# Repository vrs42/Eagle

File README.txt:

==============================================

  E A G L E - L A Y O U T - S O F T W A R E
       Information about Version 4.11

==============================================

Updating from older versions
----------------------------

IMPORTANT: If you are updating from an older version of EAGLE, please make sure
*********  you read the file doc/UPDATE.txt entirely before
           working with this new version!

Tutorial
--------

The EAGLE tutorial in PDF format can be found in the \english\tutorial
subdirectory on the EAGLE CD-ROM.
If you have downloaded EAGLE from CadSoft's homepage you may also want
to download the tutorial file.

Running the CAM Processor in batch mode
---------------------------------------

Since Windows programs give up their connection to the console they
have been started from, you can use the file 'eaglecon.exe' (located
in the 'demo' subdirectory on the CD-ROM) if you want to run the
CAM Processor from a batch file. This version of EAGLE is exactly
the same as the 'eagle.exe', except that it doesn't disconnect from
the console. Type 'eaglecon -?' for a list of CAM Processor options.

Uninstalling the Program
------------------------

In case you want to uninstall EAGLE you can click on the
"unInstallShield" icon, which has been created during installation.
This will remove all EAGLE files and registry entries, except for
files that have been created *after* the installation, like e.g.
project, schematic or board files. In that case the uninstall program
issues a message telling you that it could not remove all files.
Remove the remaining files manually from your EAGLE program directory
(default: C:\Program files\EAGLE).

Files with names like "DeIsL1.isu" in the EAGLE program directory are
necessary for the uninstallation process and should not be deleted.

Displaying and printing texts
-----------------------------

Some Windows graphics and printer drivers appear to be unable to display
texts the way EAGLE needs them to be (any size and mixed colors). If this
is the case on your system, you should either install a newer graphics
and/or printer driver, or set "Options/User interface/Always vector font"
in the EAGLE Control Panel to 'on'. With this option EAGLE always uses its
builtin vector font, which is guaranteed to work.

Printing with the PRINT Command
-------------------------------

When printing to b/w printers (like e.g. laser printers) objects may
not be visible very good. The reason for this is that the Windows
printer driver attempts to draw colors as shades of gray, which can
lead to very light shades of gray. In such cases you should use the
option "Black" to produce a pure b/w print.

Multi-Monitor Operation
-----------------------

Currently EAGLE works on multi-monitor systems only if all monitors form one
large desktop.

Mouse wheel
-----------

When a board/schematic pair is loaded and one of the windows is minimized, it
can happen that the mouse wheel won't work to zoom in and out of an editor
window. In such a case you can just click anywhere on the desktop and back on
the EAGLE editor window to activate mouse wheel support.

Octagon apertures in Gerber RS-274X format
------------------------------------------

The various Gerber viewers on the market have different ideas about how to
display octagon apertures in RS-274X format. There all all kinds of
interpretations of the diameter and rotation.
When generating octagon apertures in RS-274X format, EAGLE assumes that the
viewer will interpret the diameter as the distance between two opposite
corners, and that it has to be rotated by 22.5 degrees to achieve the proper
alignment. In case your specific viewer interprets these data differently
you can adjust this to your viewer's special needs in the file 'eagle.def'.

IMPORTANT: Before sending data in RS-274X format to your board house you should
make sure you ask them how *their* software will interpret octagon data.

                           ===================
=========================== SALES INFORMATION =================================
                           ===================

EAGLE is a program of:   CadSoft Computer, Inc.
                         801 S. Federal Hwy., Suite 201
                         Delray Beach, FL 33483-5185
                         Phone:  (561) 274-8355
                         Fax:    (561) 274-8218
                         E-Mail: info@cadsoftusa.com
                         Web:    http://www.cadsoftusa.com

EAGLE is available for Linux and Windows platforms.

===============================================================================
"Linux" is a registered trademark of Linus Torvalds.
"Windows" is a registered trademark of Microsoft Corporation.
===============================================================================

Copyright (c) 2003 CadSoft Computer, Inc. - All rights reserved

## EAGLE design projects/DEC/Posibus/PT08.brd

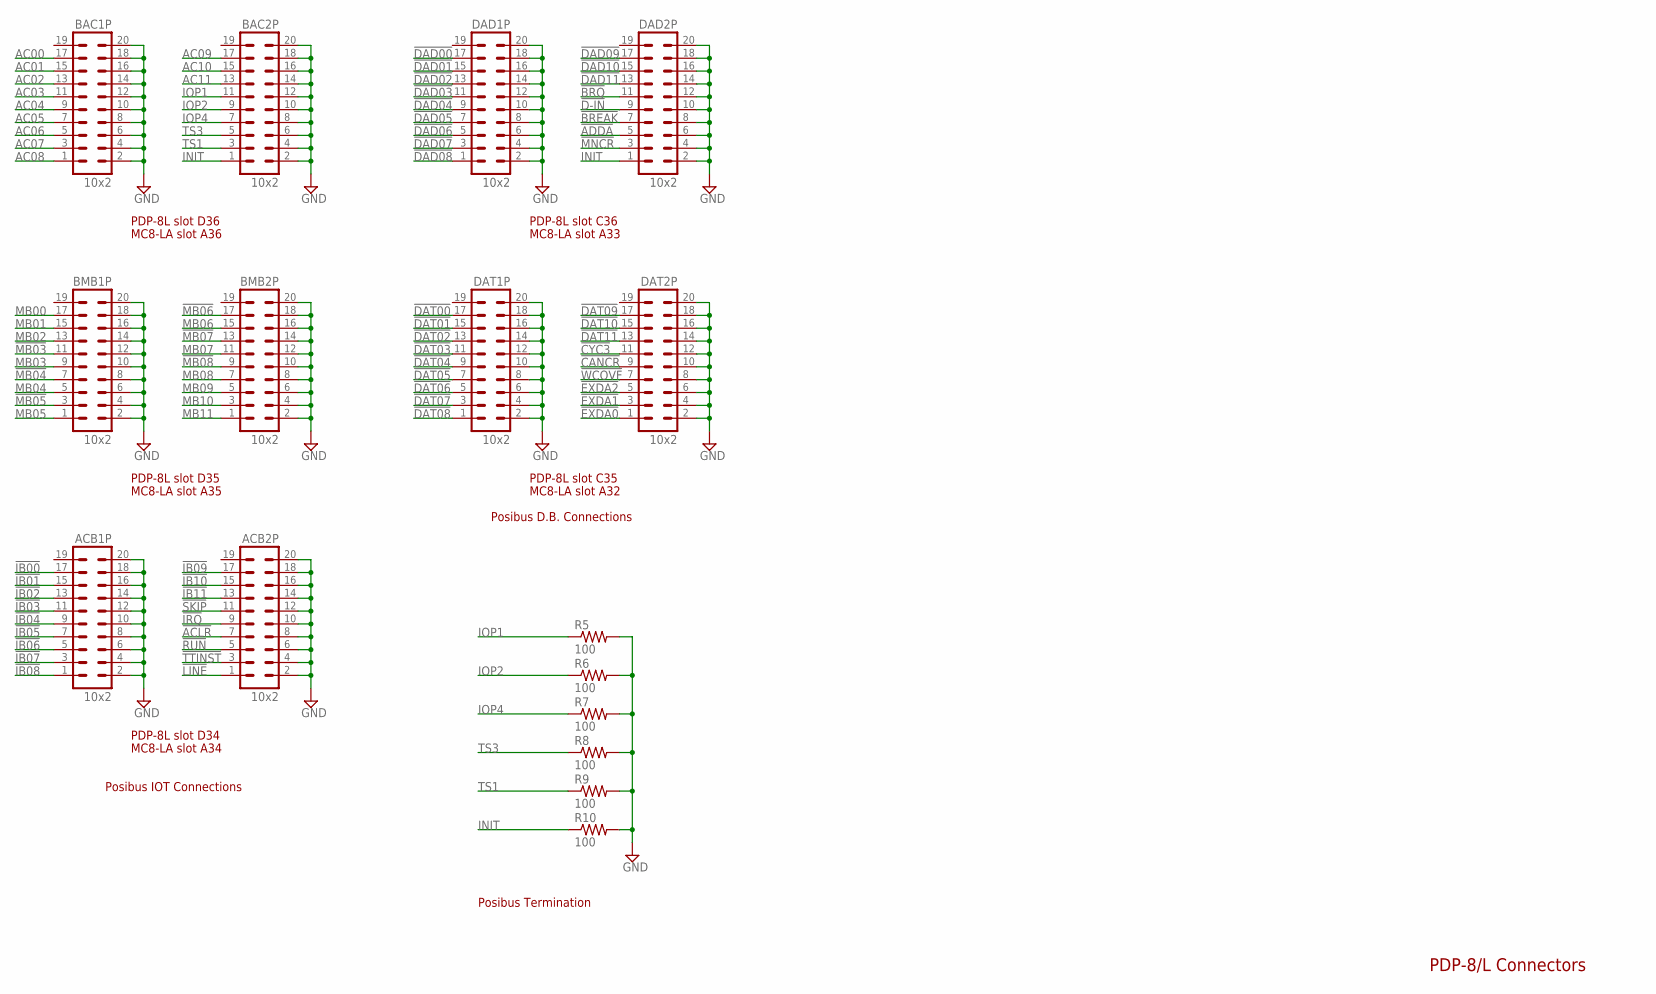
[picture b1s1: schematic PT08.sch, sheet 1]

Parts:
ACB1P, ACB2P: 10x2; MA10-2
BAC1P, BAC2P: 10x2; MA10-2
BMB1P, BMB2P: 10x2; MA10-2
DAD1P, DAD2P: 10x2; MA10-2
DAT1P, DAT2P: 10x2; MA10-2
R5, R6, R7, R8, R9, R10: 100; R1206

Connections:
!ACLR: ACB2P.7; also elsewhere on the board
!ADDA: DAD2P.5
!BREAK: DAD2P.7
!BRQ: DAD2P.11
!CANCR: DAT2P.9
!CYC3: DAT2P.11
!D-IN: DAD2P.9
!DAD00: DAD1P.17
!DAD01: DAD1P.15
!DAD02: DAD1P.13
!DAD03: DAD1P.11
!DAD04: DAD1P.9
!DAD05: DAD1P.7
!DAD06: DAD1P.5
!DAD07: DAD1P.3
!DAD08: DAD1P.1
!DAD09: DAD2P.17
!DAD10: DAD2P.15
!DAD11: DAD2P.13
!DAT00: DAT1P.17
!DAT01: DAT1P.15
!DAT02: DAT1P.13
!DAT03: DAT1P.11
!DAT04: DAT1P.9
!DAT05: DAT1P.7
!DAT06: DAT1P.5
!DAT07: DAT1P.3
!DAT08: DAT1P.1
!DAT09: DAT2P.17
!DAT10: DAT2P.15
!DAT11: DAT2P.13
!EXDA0: DAT2P.1
!EXDA1: DAT2P.3
!EXDA2: DAT2P.5
!IB00: ACB1P.17; also elsewhere on the board
!IB01: ACB1P.15; also elsewhere on the board
!IB02: ACB1P.13; also elsewhere on the board
!IB03: ACB1P.11; also elsewhere on the board
!IB04: ACB1P.9; also elsewhere on the board
!IB05: ACB1P.7; also elsewhere on the board
!IB06: ACB1P.5; also elsewhere on the board
!IB07: ACB1P.3; also elsewhere on the board
!IB08: ACB1P.1; also elsewhere on the board
!IB09: ACB2P.17; also elsewhere on the board
!IB10: ACB2P.15; also elsewhere on the board
!IB11: ACB2P.13; also elsewhere on the board
!IRQ: ACB2P.9; also elsewhere on the board
!LINE: ACB2P.1; also elsewhere on the board
!MB03: BMB1P.11
!MB04: BMB1P.7
!MB05: BMB1P.3
!MB06: BMB2P.17
!MB07: BMB2P.13
!MB08: BMB2P.9
!MNCR: DAD2P.3
!RUN: ACB2P.5; also elsewhere on the board
!SKIP: ACB2P.11; also elsewhere on the board
!TTINST: ACB2P.3; also elsewhere on the board
!WCOVF: DAT2P.7
AC00: BAC1P.17; also elsewhere on the board
AC01: BAC1P.15; also elsewhere on the board
AC02: BAC1P.13; also elsewhere on the board
AC03: BAC1P.11; also elsewhere on the board
AC04: BAC1P.9; also elsewhere on the board
AC05: BAC1P.7; also elsewhere on the board
AC06: BAC1P.5; also elsewhere on the board
AC07: BAC1P.3; also elsewhere on the board
AC08: BAC1P.1; also elsewhere on the board
AC09: BAC2P.17; also elsewhere on the board
AC10: BAC2P.15; also elsewhere on the board
AC11: BAC2P.13; also elsewhere on the board
GND: ACB1P.2, ACB1P.4, ACB1P.6, ACB1P.8, ACB1P.10, ACB1P.12, ACB1P.14, ACB1P.16, ACB1P.18, ACB1P.20, ACB2P.2, ACB2P.4, ACB2P.6, ACB2P.8, ACB2P.10, ACB2P.12, ACB2P.14, ACB2P.16, ACB2P.18, ACB2P.20, BAC1P.2, BAC1P.4, BAC1P.6, BAC1P.8, BAC1P.10, BAC1P.12, BAC1P.14, BAC1P.16, BAC1P.18, BAC1P.20, BAC2P.2, BAC2P.4, BAC2P.6, BAC2P.8, BAC2P.10, BAC2P.12, BAC2P.14, BAC2P.16, BAC2P.18, BAC2P.20, BMB1P.2, BMB1P.4, BMB1P.6, BMB1P.8, BMB1P.10, BMB1P.12, BMB1P.14, BMB1P.16, BMB1P.18, BMB1P.20, BMB2P.2, BMB2P.4, BMB2P.6, BMB2P.8, BMB2P.10, BMB2P.12, BMB2P.14, BMB2P.16, BMB2P.18, BMB2P.20, DAD1P.2, DAD1P.4, DAD1P.6, DAD1P.8, DAD1P.10, DAD1P.12, DAD1P.14, DAD1P.16, DAD1P.18, DAD1P.20, DAD2P.2, DAD2P.4, DAD2P.6, DAD2P.8, DAD2P.10, DAD2P.12, DAD2P.14, DAD2P.16, DAD2P.18, DAD2P.20, DAT1P.2, DAT1P.4, DAT1P.6, DAT1P.8, DAT1P.10, DAT1P.12, DAT1P.14, DAT1P.16, DAT1P.18, DAT1P.20, DAT2P.2, DAT2P.4, DAT2P.6, DAT2P.8, DAT2P.10, DAT2P.12, DAT2P.14, DAT2P.16, DAT2P.18, DAT2P.20, R5.2, R6.2, R7.2, R8.2, R9.2, R10.2; also elsewhere on the board
INIT: BAC2P.1, DAD2P.1, R10.1; also elsewhere on the board
IOP1: BAC2P.11, R5.1; also elsewhere on the board
IOP2: BAC2P.9, R6.1; also elsewhere on the board
IOP4: BAC2P.7, R7.1; also elsewhere on the board
MB00: BMB1P.17; also elsewhere on the board
MB01: BMB1P.15; also elsewhere on the board
MB02: BMB1P.13; also elsewhere on the board
MB03: BMB1P.9; also elsewhere on the board
MB04: BMB1P.5; also elsewhere on the board
MB05: BMB1P.1; also elsewhere on the board
MB06: BMB2P.15; also elsewhere on the board
MB07: BMB2P.11; also elsewhere on the board
MB08: BMB2P.7; also elsewhere on the board
MB09: BMB2P.5; also elsewhere on the board
MB10: BMB2P.3; also elsewhere on the board
MB11: BMB2P.1; also elsewhere on the board
TS1: BAC2P.3, R9.1; also elsewhere on the board
TS3: BAC2P.5, R8.1; also elsewhere on the board

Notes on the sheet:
Posibus IOT Connections
Posibus D.B. Connections
PDP-8/L Connectors
PDP-8L slot D35
MC8-LA slot A35
PDP-8L slot D36
MC8-LA slot A36
PDP-8L slot D34
MC8-LA slot A34
PDP-8L slot C36
MC8-LA slot A33
PDP-8L slot C35
MC8-LA slot A32
Posibus Termination

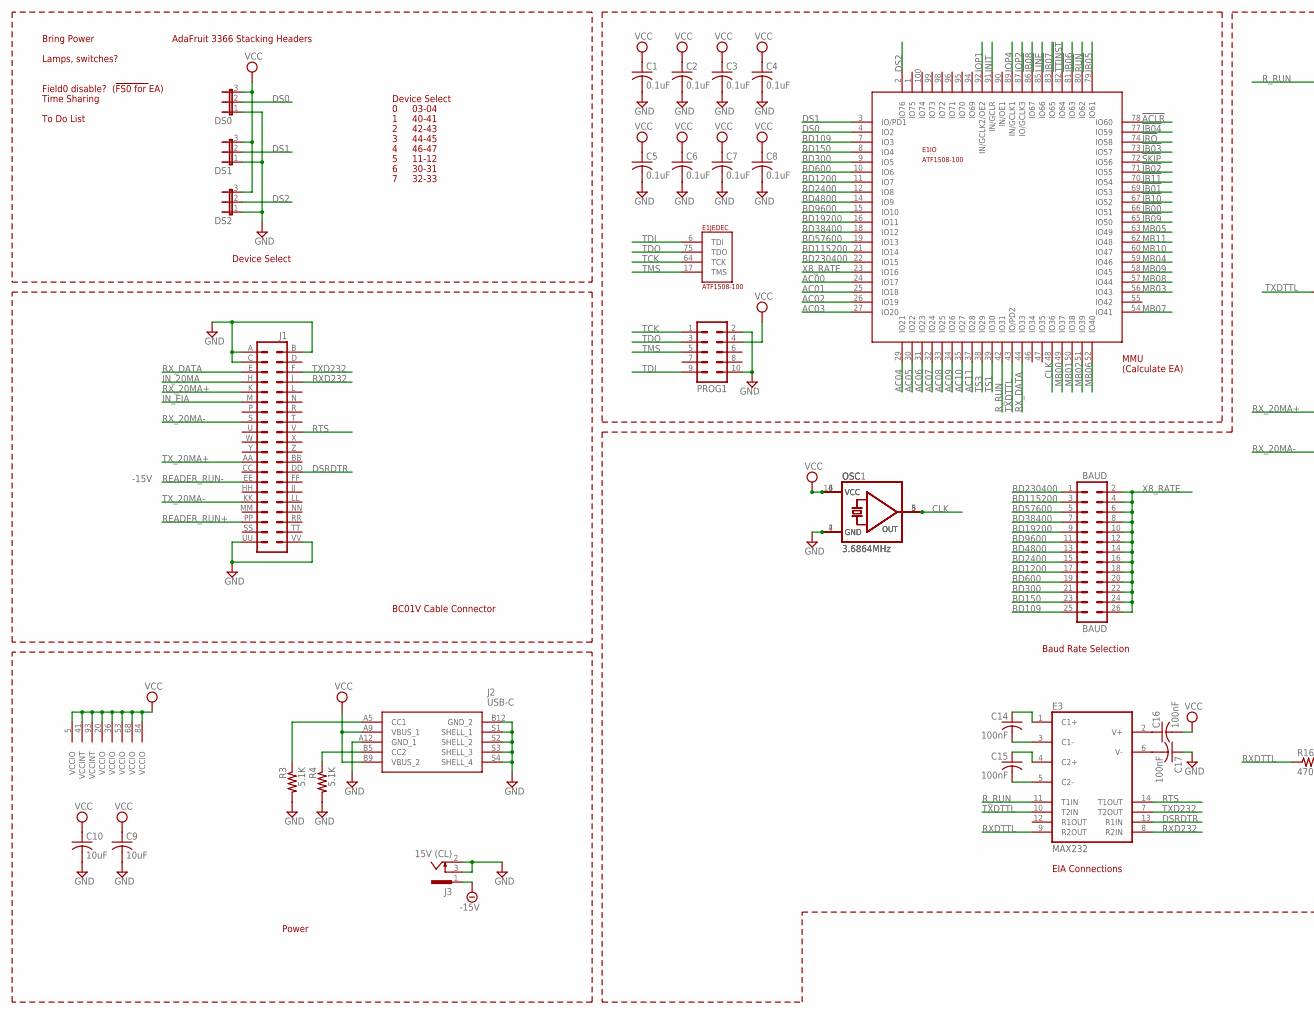
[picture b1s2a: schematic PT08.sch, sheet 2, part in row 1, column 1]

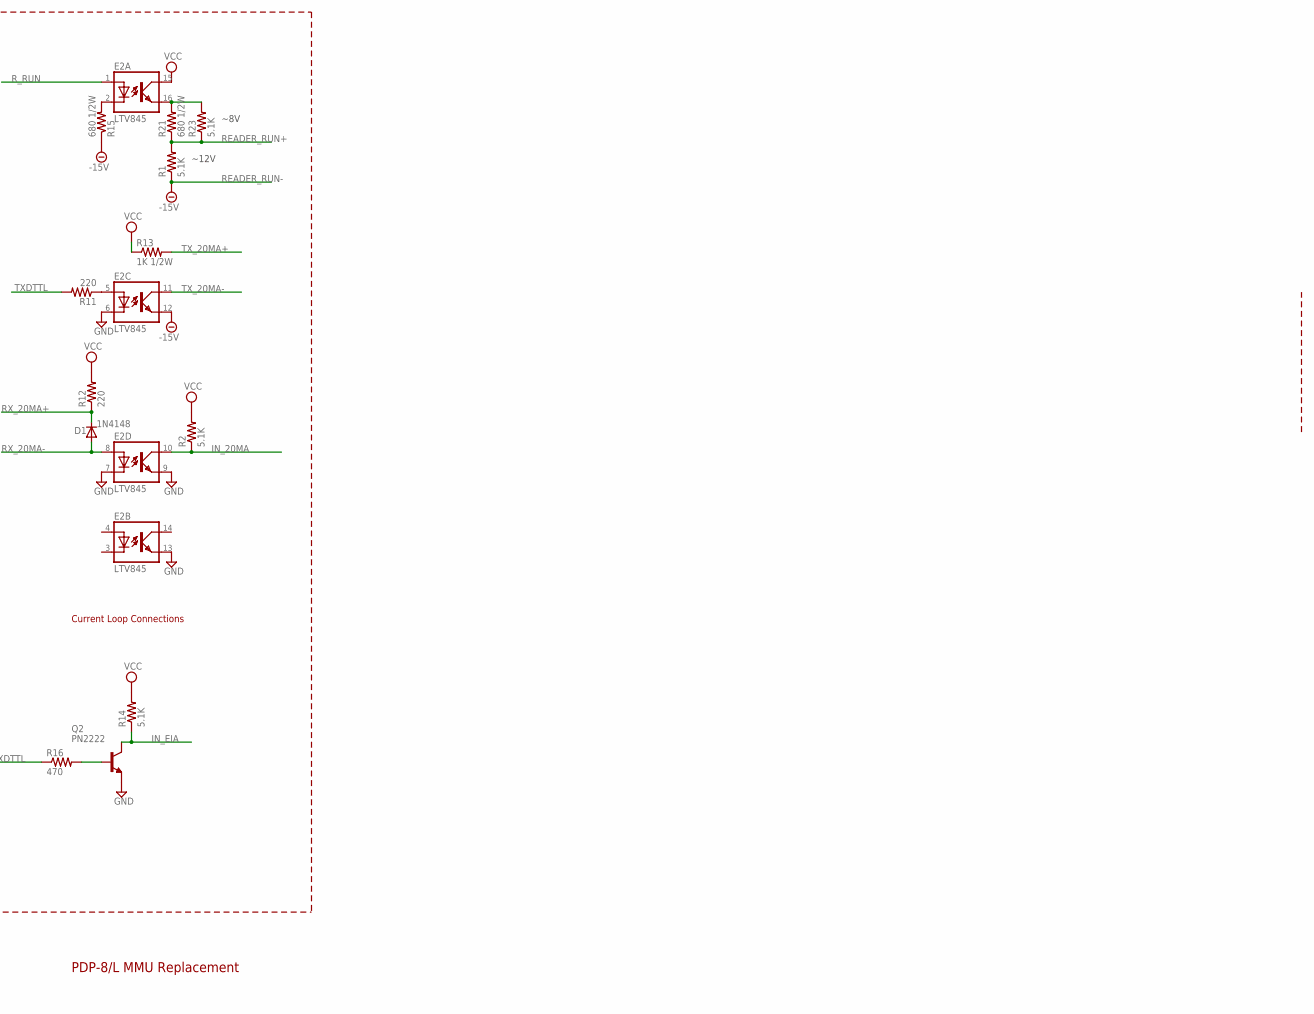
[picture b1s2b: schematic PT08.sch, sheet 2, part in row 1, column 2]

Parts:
BAUD: BAUD; MA13-2
C1, C2, C3, C4, C5, C6, C7, C8: 0.1uF; C0805
C9, C10: 10uF; C0805
C14, C15, C16, C17: 100nF; C0805
D1: 1N4148; SOD323-W
DS0, DS1, DS2: JP2
E1: ATF1508-100; PQFP-100
E2: LTV845; DIL16
E3: MAX232; DIL16
J1: DEC40PINH
J2: USB-C; USB497000A
J3: 15V (CL); SCD-014-A
OSC: 3.6864MHz; DIL08S
OSC1: 3.6864MHz; DIL14S
PROG1: ML10
Q2: PN2222; SOT23-EBC
R1, R2, R3, R4, R14, R23: 5.1K; R0805
R11, R12: 220; R0805
R13: 1K 1/2W; 0207/10
R15, R21: 680 1/2W; 0207/10
R16: 470; R0805

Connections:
!ACLR: E1.78 (IO60); also elsewhere on the board
!IB00: E1.66 (IO51); also elsewhere on the board
!IB01: E1.69 (IO53); also elsewhere on the board
!IB02: E1.71 (IO55); also elsewhere on the board
!IB03: E1.73 (IO57); also elsewhere on the board
!IB04: E1.77 (IO59); also elsewhere on the board
!IB05: E1.79 (IO61); also elsewhere on the board
!IB06: E1.81 (IO63); also elsewhere on the board
!IB07: E1.83 (IO65); also elsewhere on the board
!IB08: E1.86 (IO67); also elsewhere on the board
!IB09: E1.65 (IO50); also elsewhere on the board
!IB10: E1.67 (IO52); also elsewhere on the board
!IB11: E1.70 (IO54); also elsewhere on the board
!IRQ: E1.74 (IO58); also elsewhere on the board
!LINE: E1.85 (IO66); also elsewhere on the board
!RUN: E1.80 (IO62); also elsewhere on the board
!SKIP: E1.72 (IO56); also elsewhere on the board
!TTINST: E1.82 (IO64); also elsewhere on the board
-15V: E2.12 (EMIT), J1.EE (27), J3.1, R1.1, R15.1
AC00: E1.24 (IO17); also elsewhere on the board
AC01: E1.25 (IO18); also elsewhere on the board
AC02: E1.26 (IO19); also elsewhere on the board
AC03: E1.27 (IO20); also elsewhere on the board
AC04: E1.29 (IO21); also elsewhere on the board
AC05: E1.30 (IO22); also elsewhere on the board
AC06: E1.31 (IO23); also elsewhere on the board
AC07: E1.32 (IO24); also elsewhere on the board
AC08: E1.33 (IO25); also elsewhere on the board
AC09: E1.34 (IO26); also elsewhere on the board
AC10: E1.35 (IO27); also elsewhere on the board
AC11: E1.37 (IO28); also elsewhere on the board
BD109: BAUD.25, E1.7 (IO3)
BD150: BAUD.23, E1.8 (IO4)
BD300: BAUD.21, E1.9 (IO5)
BD600: BAUD.19, E1.10 (IO6)
BD1200: BAUD.17, E1.11 (IO7)
BD2400: BAUD.15, E1.12 (IO8)
BD4800: BAUD.13, E1.14 (IO9)
BD9600: BAUD.11, E1.15 (IO10)
BD19200: BAUD.9, E1.16 (IO11)
BD38400: BAUD.7, E1.18 (IO12)
BD57600: BAUD.5, E1.19 (IO13)
BD115200: BAUD.3, E1.21 (IO14)
BD230400: BAUD.1, E1.22 (IO15)
CLK: E1.48 (IO36), OSC.5 (OUT), OSC1.8 (OUT)
DS0: DS0.2, E1.4 (IO2)
DS1: DS1.2, E1.3 (IO/PD1)
DS2: DS2.2, E1.2 (IO76)
DSRDTR: E3.13 (R1IN), J1.DD (26)
GND: C1.2, C2.2, C3.2, C4.2, C5.2, C6.2, C7.2, C8.2, C9.2, C10.2, C17.1, DS0.1, DS1.1, DS2.1, E1.13 (GND), E1.28 (GND), E1.40 (GND), E1.45 (GND), E1.61 (GND), E1.76 (GND), E1.88 (GND), E1.97 (GND), E2.6 (C), E2.7 (C), E2.9 (EMIT), E2.13 (EMIT), E3.15 (GND), J1.A (1), J1.B (2), J1.C (3), J1.UU (39), J1.VV (40), J2.A12 (GND_1), J2.B12 (GND_2), J2.S1 (SHELL_1), J2.S2 (SHELL_2), J2.S3 (SHELL_3), J2.S4 (SHELL_4), J3.2, J3.3, OSC.4 (GND), OSC1.7 (GND), PROG1.2, PROG1.10, Q2.E, R3.2, R4.2; also elsewhere on the board
INIT: E1.91 (IN/GCLR); also elsewhere on the board
IN_20MA: E2.10 (COL), J1.H (7), R2.1
IN_EIA: J1.M (11), Q2.C, R14.1
IOP1: E1.92 (IN/GCLK2/OE2); also elsewhere on the board
IOP2: E1.87 (IO/GCLK3); also elsewhere on the board
IOP4: E1.89 (IN/GCLK1); also elsewhere on the board
MB00: E1.49 (IO37); also elsewhere on the board
MB01: E1.50 (IO38); also elsewhere on the board
MB02: E1.51 (IO39); also elsewhere on the board
MB03: E1.56 (IO43); also elsewhere on the board
MB04: E1.59 (IO46); also elsewhere on the board
MB05: E1.63 (IO49); also elsewhere on the board
MB06: E1.52 (IO40); also elsewhere on the board
MB07: E1.54 (IO41); also elsewhere on the board
MB08: E1.57 (IO44); also elsewhere on the board
MB09: E1.58 (IO45); also elsewhere on the board
MB10: E1.60 (IO47); also elsewhere on the board
MB11: E1.62 (IO48); also elsewhere on the board
unnamed: J2.B5 (CC2), R4.1
unnamed: E2.2 (C), R15.2
unnamed: J2.A5 (CC1), R3.1
unnamed: E2.16 (EMIT), R21.2, R23.2
unnamed: Q2.B, R16.2
unnamed: E2.5 (A), R11.1
unnamed: C17.2, E3.6 (V-)
unnamed: C14.1, E3.1 (C1+)
unnamed: C14.2, E3.3 (C1-)
unnamed: C15.2, E3.5 (C2-)
unnamed: C15.1, E3.4 (C2+)
unnamed: C16.1, E3.2 (V+)
READER_RUN+: J1.PP (35), R1.2, R21.1, R23.1
RTS: E3.14 (T1OUT), J1.V (18)
RXD232: E3.8 (R2IN), J1.J (8)
RXDTTL: E3.9 (R2OUT), R16.1
RX_20MA+: D1.C, J1.K (9), R12.1
RX_20MA-: D1.A, E2.8 (A), J1.S (15)
RX_DATA: E1.44 (IO33), J1.E (5)
R_RUN: E1.42 (IO31), E2.1 (A), E3.11 (T1IN)
TCK: E1.64 (TCK), PROG1.1
TDI: E1.6 (TDI), PROG1.9
TDO: E1.75 (TDO), PROG1.3
TMS: E1.17 (TMS), PROG1.5
TS1: E1.39 (IO30); also elsewhere on the board
TS3: E1.38 (IO29); also elsewhere on the board
TXD232: E3.7 (T2OUT), J1.F (6)
TXDTTL: E1.43 (IO/PD2), E3.10 (T2IN), R11.2
TX_20MA+: J1.AA (23), R13.2
TX_20MA-: E2.11 (COL), J1.KK (31)
VCC: C1.1, C2.1, C3.1, C4.1, C5.1, C6.1, C7.1, C8.1, C9.1, C10.1, C16.2, DS0.3, DS1.3, DS2.3, E1.5 (VCCIO), E1.20 (VCCIO), E1.36 (VCCIO), E1.41 (VCCINT), E1.53 (VCCIO), E1.68 (VCCIO), E1.84 (VCCIO), E1.93 (VCCINT), E2.15 (COL), E3.16 (VCC), J2.A9 (VBUS_1), J2.B9 (VBUS_2), OSC.8 (VCC), OSC1.14 (VCC), PROG1.4, R2.2, R12.2, R13.1, R14.2
X8_RATE: BAUD.2, BAUD.4, BAUD.6, BAUD.8, BAUD.10, BAUD.12, BAUD.14, BAUD.16, BAUD.18, BAUD.20, BAUD.22, BAUD.24, BAUD.26, E1.23 (IO16)

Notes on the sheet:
PDP-8/L MMU Replacement
Bring Power
Lamps, switches?
Field0 disable?
Time Sharing
To Do List
(!FS0 for !EA)
AdaFruit 3366 Stacking Headers
MMU
(Calculate EA)
Power
Device Select
EIA Connections
Current Loop Connections
~8V
~12V
READER_RUN-
BC01V Cable Connector
Baud Rate Selection
03-04
40-41
42-43
44-45
46-47
11-12
30-31
32-33

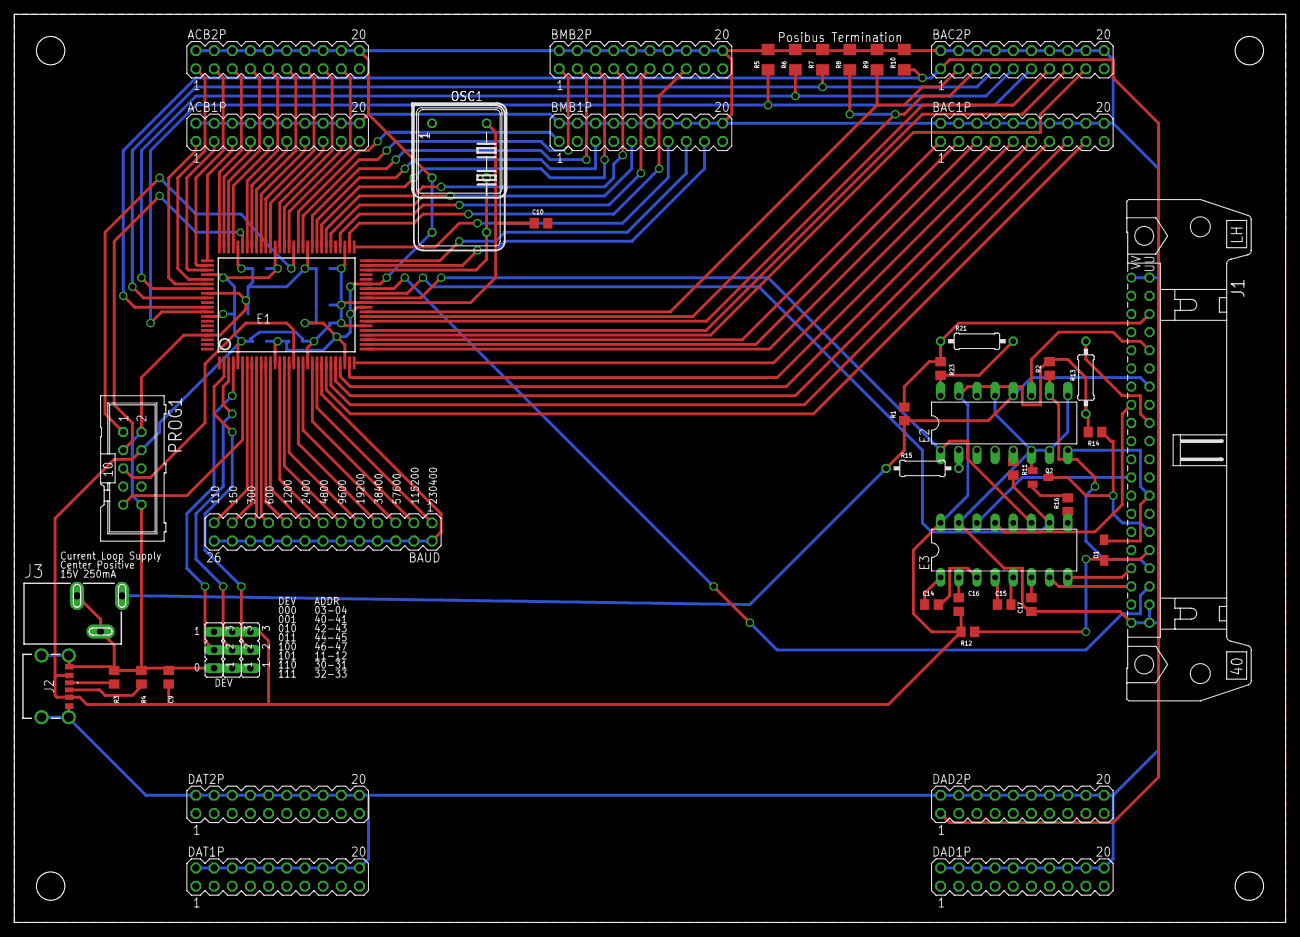
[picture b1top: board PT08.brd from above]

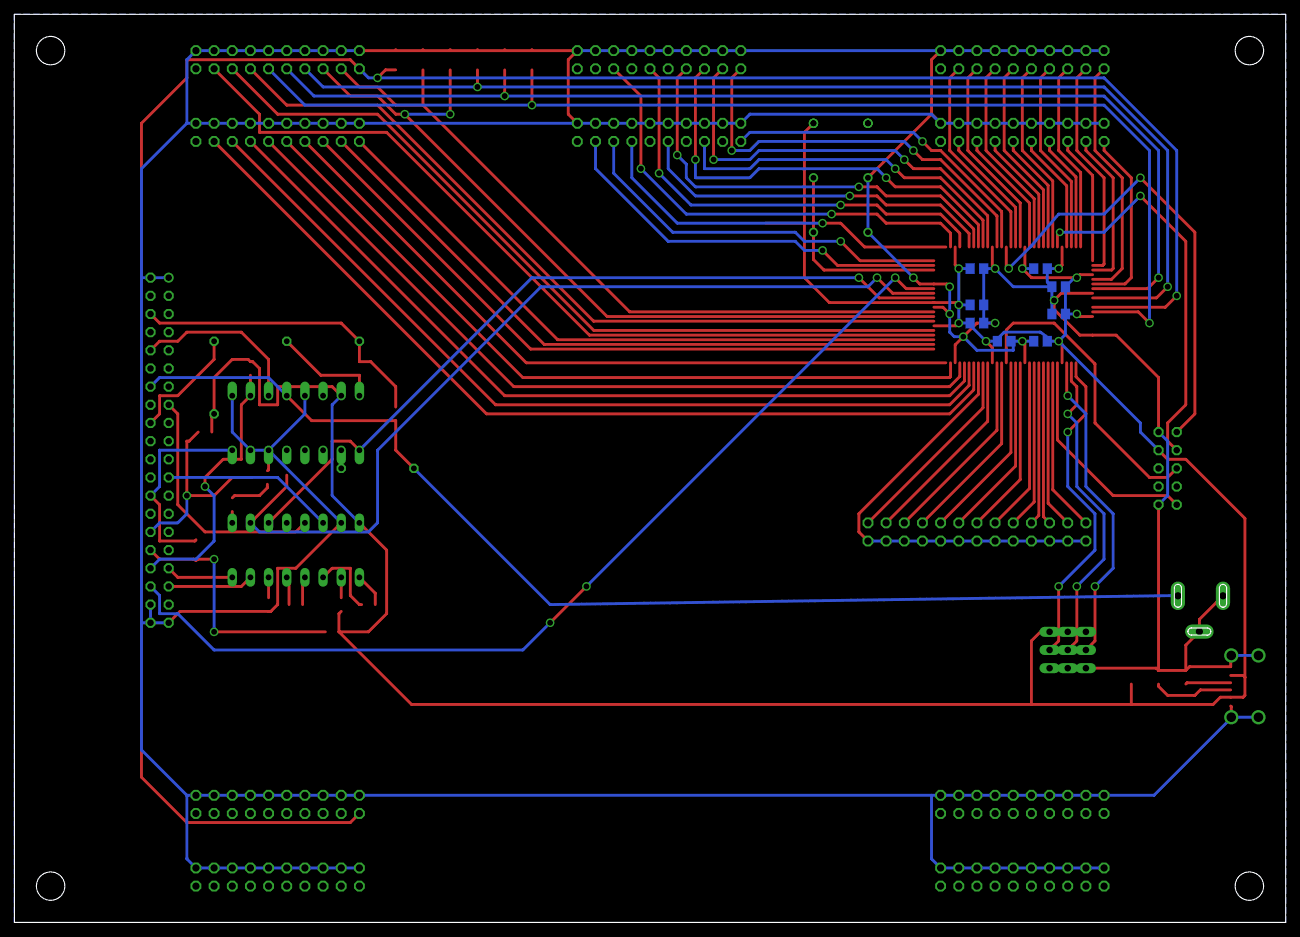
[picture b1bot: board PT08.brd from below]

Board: 2 copper layers, 177.8 x 127.0 mm, 57 parts (8 on the bottom side), 100 nets.

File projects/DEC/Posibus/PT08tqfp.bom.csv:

Comment,Designator,Footprint,PartNo
0.1uF,C5,C0805,C5378
0.1uF,C4,C0805,C5378
0.1uF,C2,C0805,C5378
0.1uF,C6,C0805,C5378
0.1uF,C3,C0805,C5378
ATF1508-100,E1,TQFP-100,C1521282
0.1uF,C1,C0805,C5378
0.1uF,C7,C0805,C5378
0.1uF,C8,C0805,C5378
5.1K,R4,R0805,C27834
5.1K,R3,R0805,C27834
100,R5,R1206,C17901
100,R6,R1206,C17901
100,R7,R1206,C17901
100,R8,R1206,C17901
100,R9,R1206,C17901
100,R10,R1206,C17901
100nF,C14,C0805,C5378
100nF,C15,C0805,C5378
100nF,C16,C0805,C5378
100nF,C17,C0805,C5378
5.1K,R1,R0805,C27834
5.1K,R2,R0805,C27834
220,R11,R0805,C17557
220,R12,R0805,C17557
1N4148,D1,SOD323-W,C2128
5.1K,R23,R0805,C27834
5.1K,R14,R0805,C27834
470,R16,R0805,C17710
PN2222,Q2,SOT23-EBC,C8512
10uF,C9,C0805,C15850
10uF,C10,C0805,C15850

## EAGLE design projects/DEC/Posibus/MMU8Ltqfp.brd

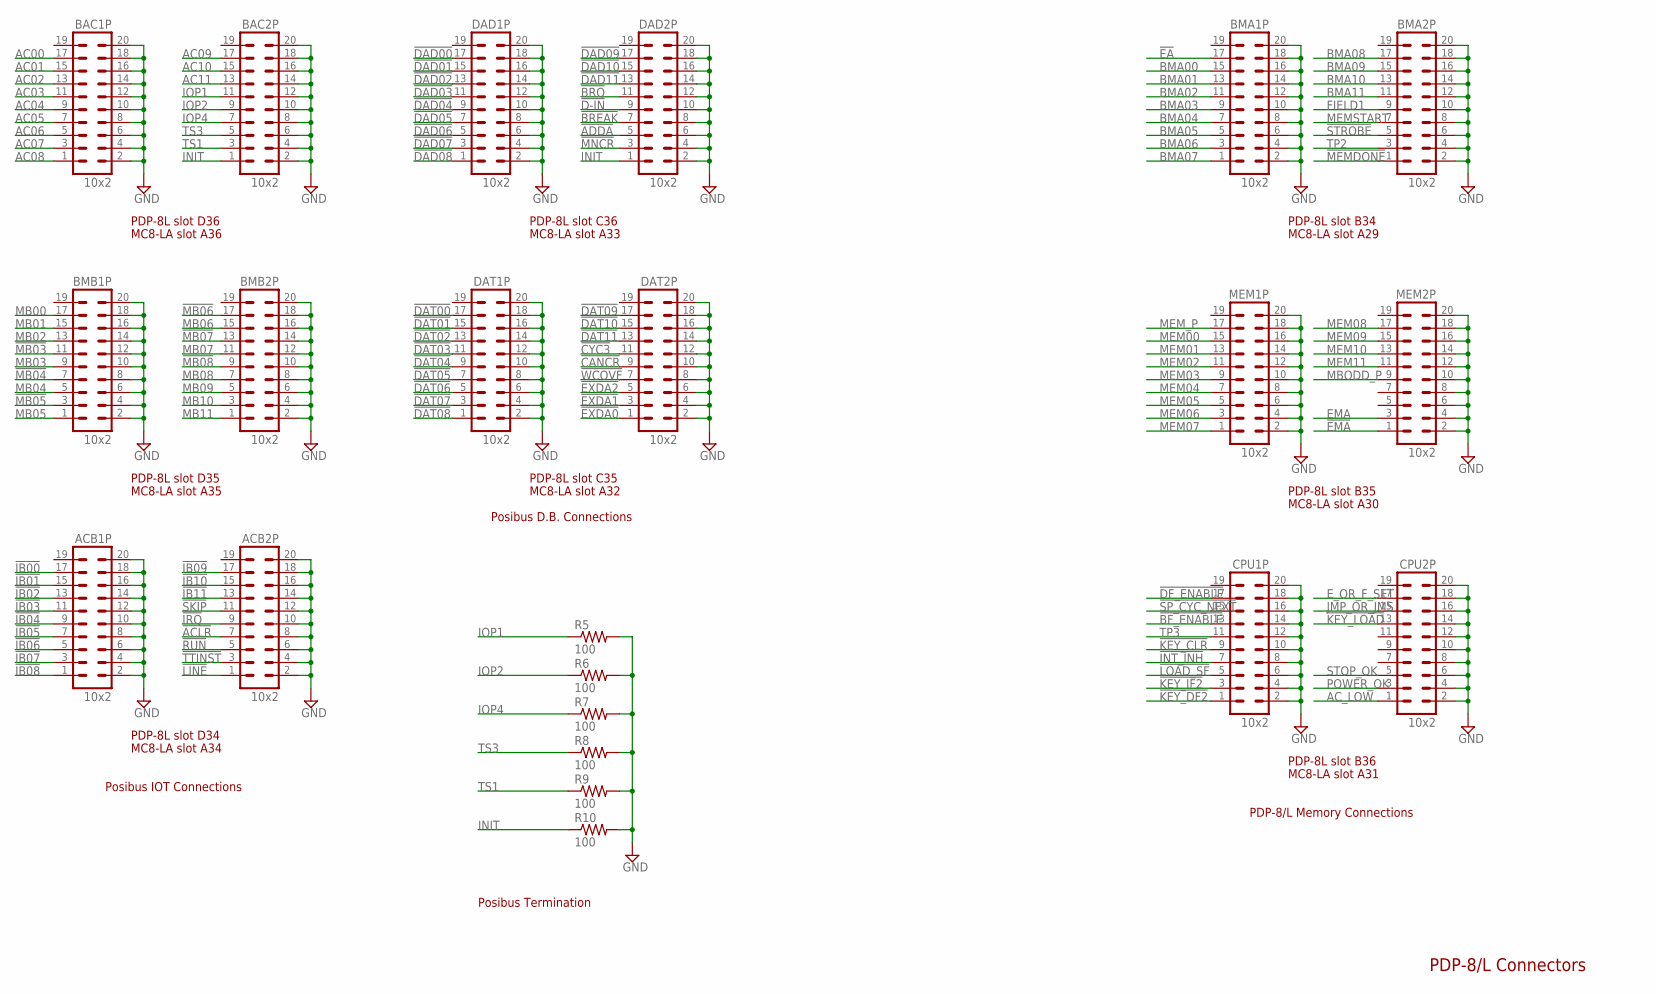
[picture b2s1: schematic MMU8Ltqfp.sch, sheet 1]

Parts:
ACB1P, ACB2P: 10x2; MA10-2
BAC1P, BAC2P: 10x2; MA10-2
BMA1P, BMA2P: 10x2; MA10-2
BMB1P, BMB2P: 10x2; MA10-2
CPU1P, CPU2P: 10x2; MA10-2
DAD1P, DAD2P: 10x2; MA10-2
DAT1P, DAT2P: 10x2; MA10-2
MEM1P, MEM2P: 10x2; MA10-2
R5, R6, R7, R8, R9, R10: 100; R1206

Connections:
!ACLR: ACB2P.7; also elsewhere on the board
!ADDA: DAD2P.5
!BF_ENABLE: CPU1P.13; also elsewhere on the board
!BREAK: DAD2P.7
!BRQ: DAD2P.11
!CANCR: DAT2P.9
!CYC3: DAT2P.11
!D-IN: DAD2P.9
!DAD00: DAD1P.17
!DAD01: DAD1P.15
!DAD02: DAD1P.13
!DAD03: DAD1P.11
!DAD04: DAD1P.9
!DAD05: DAD1P.7
!DAD06: DAD1P.5
!DAD07: DAD1P.3
!DAD08: DAD1P.1
!DAD09: DAD2P.17
!DAD10: DAD2P.15
!DAD11: DAD2P.13
!DAT00: DAT1P.17
!DAT01: DAT1P.15
!DAT02: DAT1P.13
!DAT03: DAT1P.11
!DAT04: DAT1P.9
!DAT05: DAT1P.7
!DAT06: DAT1P.5
!DAT07: DAT1P.3
!DAT08: DAT1P.1
!DAT09: DAT2P.17
!DAT10: DAT2P.15
!DAT11: DAT2P.13
!DF_ENABLE: CPU1P.17; also elsewhere on the board
!EA: BMA1P.17; also elsewhere on the board
!EMA: MEM2P.1; also elsewhere on the board
!EXDA0: DAT2P.1; also elsewhere on the board
!EXDA1: DAT2P.3; also elsewhere on the board
!EXDA2: DAT2P.5; also elsewhere on the board
!IB00: ACB1P.17; also elsewhere on the board
!IB01: ACB1P.15; also elsewhere on the board
!IB02: ACB1P.13; also elsewhere on the board
!IB03: ACB1P.11; also elsewhere on the board
!IB04: ACB1P.9; also elsewhere on the board
!IB05: ACB1P.7; also elsewhere on the board
!IB06: ACB1P.5; also elsewhere on the board
!IB07: ACB1P.3; also elsewhere on the board
!IB08: ACB1P.1; also elsewhere on the board
!IB09: ACB2P.17; also elsewhere on the board
!IB10: ACB2P.15; also elsewhere on the board
!IB11: ACB2P.13; also elsewhere on the board
!INT_INH: CPU1P.7; also elsewhere on the board
!IRQ: ACB2P.9; also elsewhere on the board
!KEY_CLR: CPU1P.9; also elsewhere on the board
!KEY_DF2: CPU1P.1; also elsewhere on the board
!KEY_IF2: CPU1P.3; also elsewhere on the board
!KEY_LOAD: CPU2P.13; also elsewhere on the board
!LINE: ACB2P.1; also elsewhere on the board
!LOAD_SF: CPU1P.5; also elsewhere on the board
!MB03: BMB1P.11
!MB04: BMB1P.7
!MB05: BMB1P.3
!MB06: BMB2P.17
!MB07: BMB2P.13
!MB08: BMB2P.9
!MEMDONE: BMA2P.1; also elsewhere on the board
!MNCR: DAD2P.3
!RUN: ACB2P.5; also elsewhere on the board
!SKIP: ACB2P.11; also elsewhere on the board
!SP_CYC_NEXT: CPU1P.15; also elsewhere on the board
!STROBE: BMA2P.5; also elsewhere on the board
!TTINST: ACB2P.3; also elsewhere on the board
!WCOVF: DAT2P.7
AC00: BAC1P.17
AC01: BAC1P.15
AC02: BAC1P.13
AC03: BAC1P.11
AC04: BAC1P.9
AC05: BAC1P.7
AC06: BAC1P.5
AC07: BAC1P.3
AC08: BAC1P.1
AC09: BAC2P.17
AC10: BAC2P.15
AC11: BAC2P.13
AC_LOW: CPU2P.1; also elsewhere on the board
BMA00: BMA1P.15; also elsewhere on the board
BMA01: BMA1P.13; also elsewhere on the board
BMA02: BMA1P.11; also elsewhere on the board
BMA03: BMA1P.9; also elsewhere on the board
BMA04: BMA1P.7; also elsewhere on the board
BMA05: BMA1P.5; also elsewhere on the board
BMA06: BMA1P.3; also elsewhere on the board
BMA07: BMA1P.1; also elsewhere on the board
BMA08: BMA2P.17; also elsewhere on the board
BMA09: BMA2P.15; also elsewhere on the board
BMA10: BMA2P.13; also elsewhere on the board
BMA11: BMA2P.11; also elsewhere on the board
EMA: MEM2P.3; also elsewhere on the board
E_OR_F_SET: CPU2P.17; also elsewhere on the board
FIELD1: BMA2P.9; also elsewhere on the board
GND: ACB1P.2, ACB1P.4, ACB1P.6, ACB1P.8, ACB1P.10, ACB1P.12, ACB1P.14, ACB1P.16, ACB1P.18, ACB1P.20, ACB2P.2, ACB2P.4, ACB2P.6, ACB2P.8, ACB2P.10, ACB2P.12, ACB2P.14, ACB2P.16, ACB2P.18, ACB2P.20, BAC1P.2, BAC1P.4, BAC1P.6, BAC1P.8, BAC1P.10, BAC1P.12, BAC1P.14, BAC1P.16, BAC1P.18, BAC1P.20, BAC2P.2, BAC2P.4, BAC2P.6, BAC2P.8, BAC2P.10, BAC2P.12, BAC2P.14, BAC2P.16, BAC2P.18, BAC2P.20, BMA1P.2, BMA1P.4, BMA1P.6, BMA1P.8, BMA1P.10, BMA1P.12, BMA1P.14, BMA1P.16, BMA1P.18, BMA1P.20, BMA2P.2, BMA2P.4, BMA2P.6, BMA2P.8, BMA2P.10, BMA2P.12, BMA2P.14, BMA2P.16, BMA2P.18, BMA2P.20, BMB1P.2, BMB1P.4, BMB1P.6, BMB1P.8, BMB1P.10, BMB1P.12, BMB1P.14, BMB1P.16, BMB1P.18, BMB1P.20, BMB2P.2, BMB2P.4, BMB2P.6, BMB2P.8, BMB2P.10, BMB2P.12, BMB2P.14, BMB2P.16, BMB2P.18, BMB2P.20, CPU1P.2, CPU1P.4, CPU1P.6, CPU1P.8, CPU1P.10, CPU1P.12, CPU1P.14, CPU1P.16, CPU1P.18, CPU1P.20, CPU2P.2, CPU2P.4, CPU2P.6, CPU2P.8, CPU2P.10, CPU2P.12, CPU2P.14, CPU2P.16, CPU2P.18, CPU2P.20, DAD1P.2, DAD1P.4, DAD1P.6, DAD1P.8, DAD1P.10, DAD1P.12, DAD1P.14, DAD1P.16, DAD1P.18, DAD1P.20, DAD2P.2, DAD2P.4, DAD2P.6, DAD2P.8, DAD2P.10, DAD2P.12, DAD2P.14, DAD2P.16, DAD2P.18, DAD2P.20, DAT1P.2, DAT1P.4, DAT1P.6, DAT1P.8, DAT1P.10, DAT1P.12, DAT1P.14, DAT1P.16, DAT1P.18, DAT1P.20, DAT2P.2, DAT2P.4, DAT2P.6, DAT2P.8, DAT2P.10, DAT2P.12, DAT2P.14, DAT2P.16, DAT2P.18, DAT2P.20, MEM1P.2, MEM1P.4, MEM1P.6, MEM1P.8, MEM1P.10, MEM1P.12, MEM1P.14, MEM1P.16, MEM1P.18, MEM1P.20, MEM2P.2, MEM2P.4, MEM2P.6, MEM2P.8, MEM2P.10, MEM2P.12, MEM2P.14, MEM2P.16, MEM2P.18, MEM2P.20, R5.2, R6.2, R7.2, R8.2, R9.2, R10.2; also elsewhere on the board
INIT: BAC2P.1, DAD2P.1, R10.1; also elsewhere on the board
IOP1: BAC2P.11, R5.1; also elsewhere on the board
IOP2: BAC2P.9, R6.1; also elsewhere on the board
IOP4: BAC2P.7, R7.1; also elsewhere on the board
JMP_OR_JMS: CPU2P.15; also elsewhere on the board
MB00: BMB1P.17; also elsewhere on the board
MB01: BMB1P.15; also elsewhere on the board
MB02: BMB1P.13; also elsewhere on the board
MB03: BMB1P.9; also elsewhere on the board
MB04: BMB1P.5; also elsewhere on the board
MB05: BMB1P.1; also elsewhere on the board
MB06: BMB2P.15; also elsewhere on the board
MB07: BMB2P.11; also elsewhere on the board
MB08: BMB2P.7; also elsewhere on the board
MB09: BMB2P.5; also elsewhere on the board
MB10: BMB2P.3; also elsewhere on the board
MB11: BMB2P.1; also elsewhere on the board
MBODD_P: MEM2P.9; also elsewhere on the board
MEM00: MEM1P.15; also elsewhere on the board
MEM01: MEM1P.13; also elsewhere on the board
MEM02: MEM1P.11; also elsewhere on the board
MEM03: MEM1P.9; also elsewhere on the board
MEM04: MEM1P.7; also elsewhere on the board
MEM05: MEM1P.5; also elsewhere on the board
MEM06: MEM1P.3; also elsewhere on the board
MEM07: MEM1P.1; also elsewhere on the board
MEM08: MEM2P.17; also elsewhere on the board
MEM09: MEM2P.15; also elsewhere on the board
MEM10: MEM2P.13; also elsewhere on the board
MEM11: MEM2P.11; also elsewhere on the board
MEMSTART: BMA2P.7; also elsewhere on the board
MEM_P: MEM1P.17; also elsewhere on the board
POWER_OK: CPU2P.3; also elsewhere on the board
STOP_OK: CPU2P.5; also elsewhere on the board
TP2: BMA2P.3; also elsewhere on the board
TP3: CPU1P.11; also elsewhere on the board
TS1: BAC2P.3, R9.1
TS3: BAC2P.5, R8.1

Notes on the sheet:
Posibus IOT Connections
Posibus D.B. Connections
PDP-8/L Connectors
PDP-8/L Memory Connections
PDP-8L slot D35
MC8-LA slot A35
PDP-8L slot D36
MC8-LA slot A36
PDP-8L slot D34
MC8-LA slot A34
PDP-8L slot B34
MC8-LA slot A29
PDP-8L slot B35
MC8-LA slot A30
PDP-8L slot B36
MC8-LA slot A31
PDP-8L slot C36
MC8-LA slot A33
PDP-8L slot C35
MC8-LA slot A32
Posibus Termination
